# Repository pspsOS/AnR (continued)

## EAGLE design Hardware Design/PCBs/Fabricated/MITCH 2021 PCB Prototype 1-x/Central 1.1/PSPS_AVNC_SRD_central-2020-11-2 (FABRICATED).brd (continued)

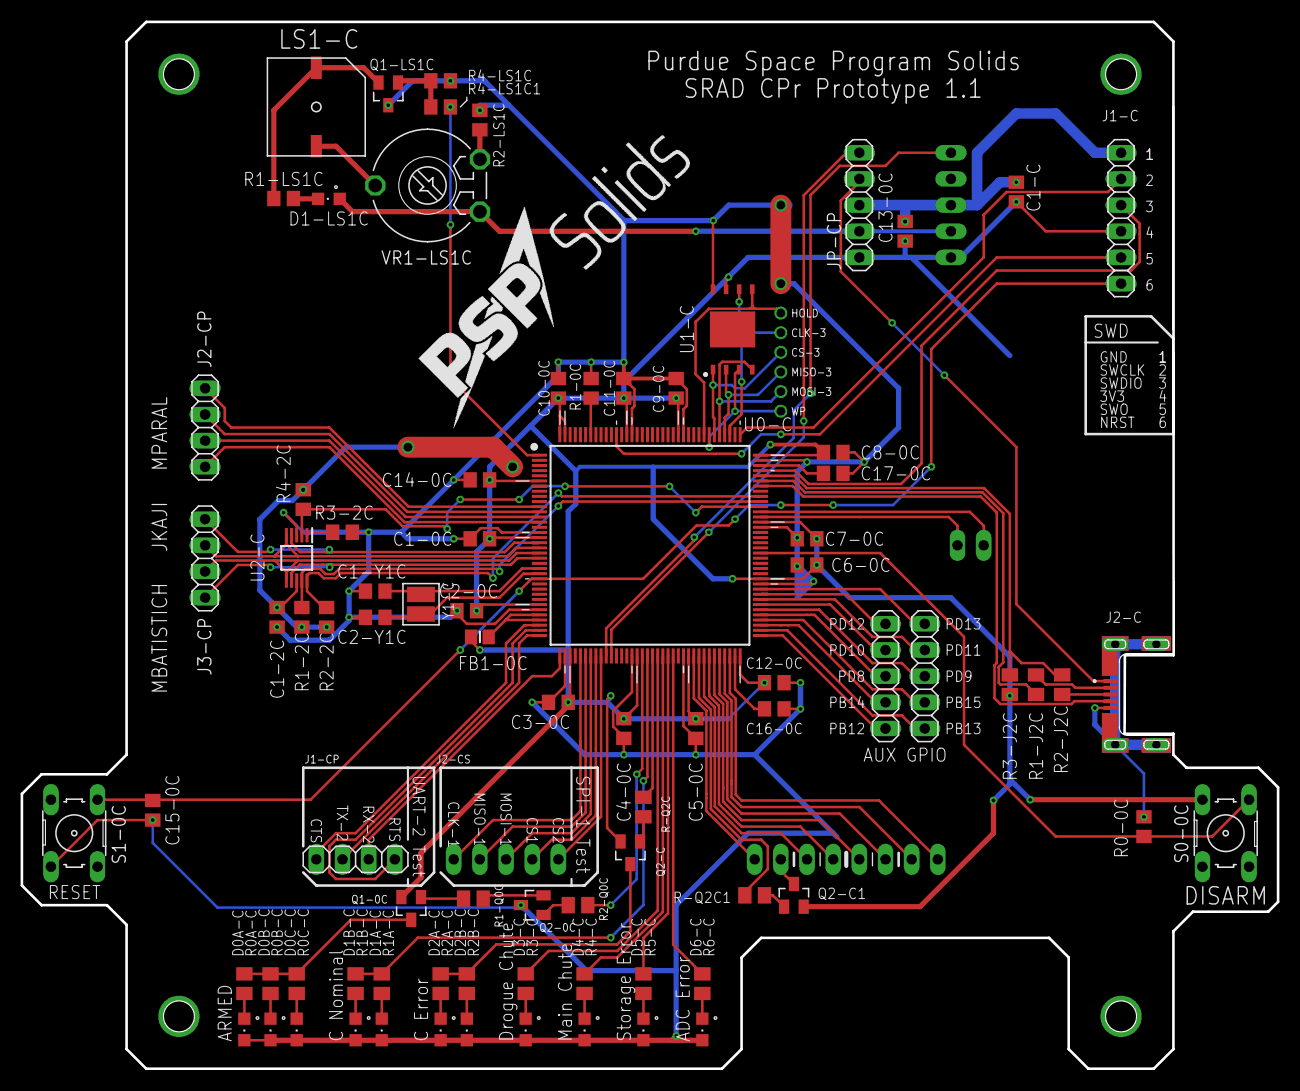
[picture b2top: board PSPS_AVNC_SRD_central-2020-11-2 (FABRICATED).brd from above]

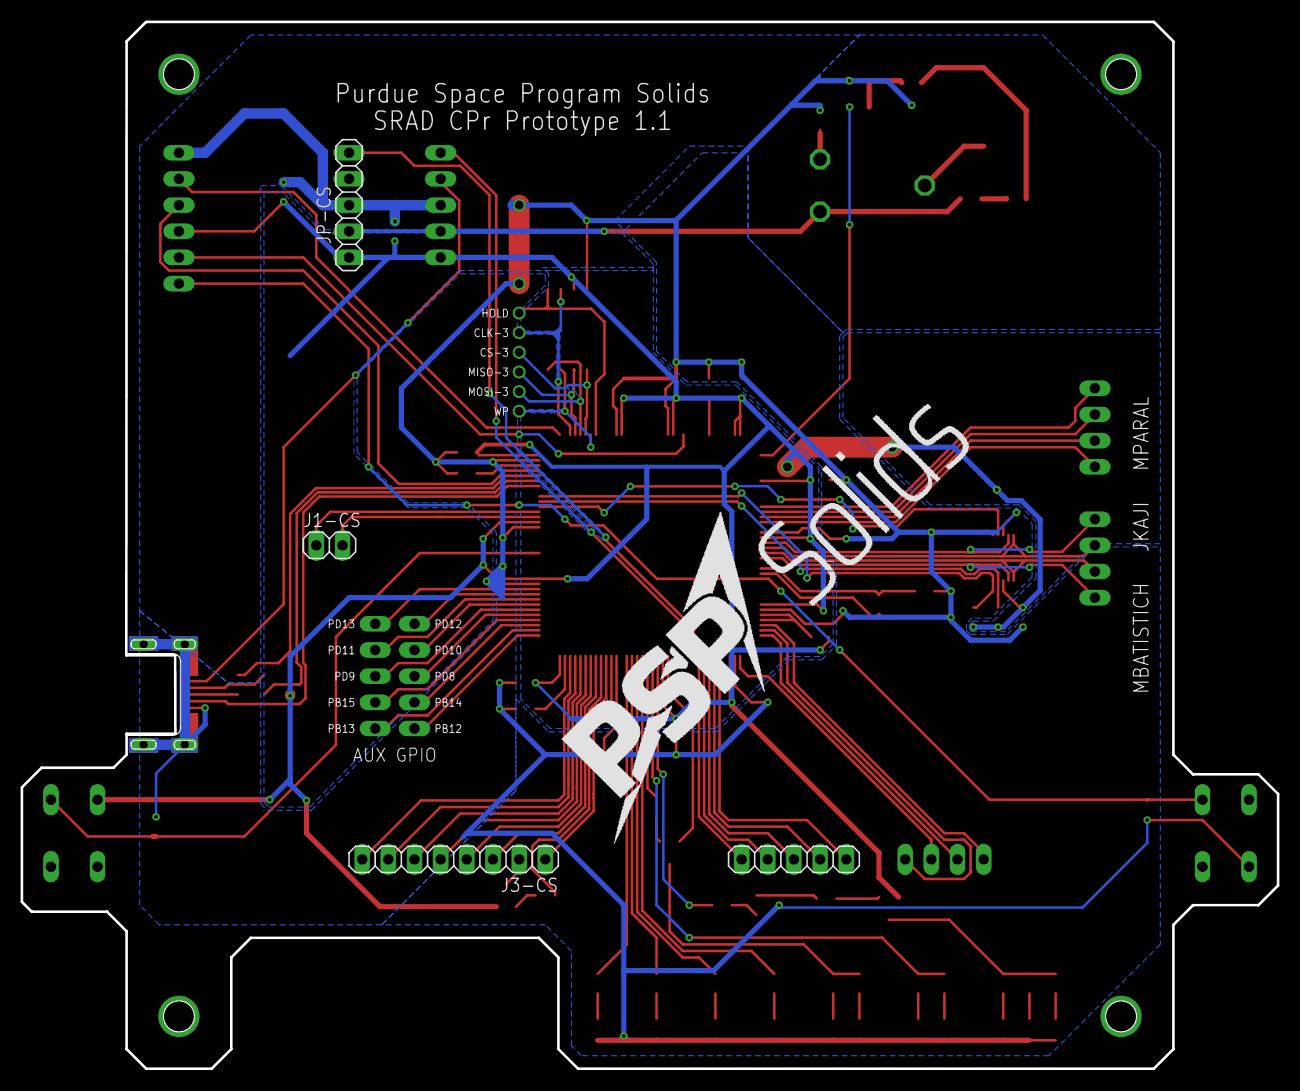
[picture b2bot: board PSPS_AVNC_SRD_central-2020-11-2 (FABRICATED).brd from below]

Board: 2 copper layers, 121.9 x 101.6 mm, 87 parts (4 on the bottom side), 101 nets.

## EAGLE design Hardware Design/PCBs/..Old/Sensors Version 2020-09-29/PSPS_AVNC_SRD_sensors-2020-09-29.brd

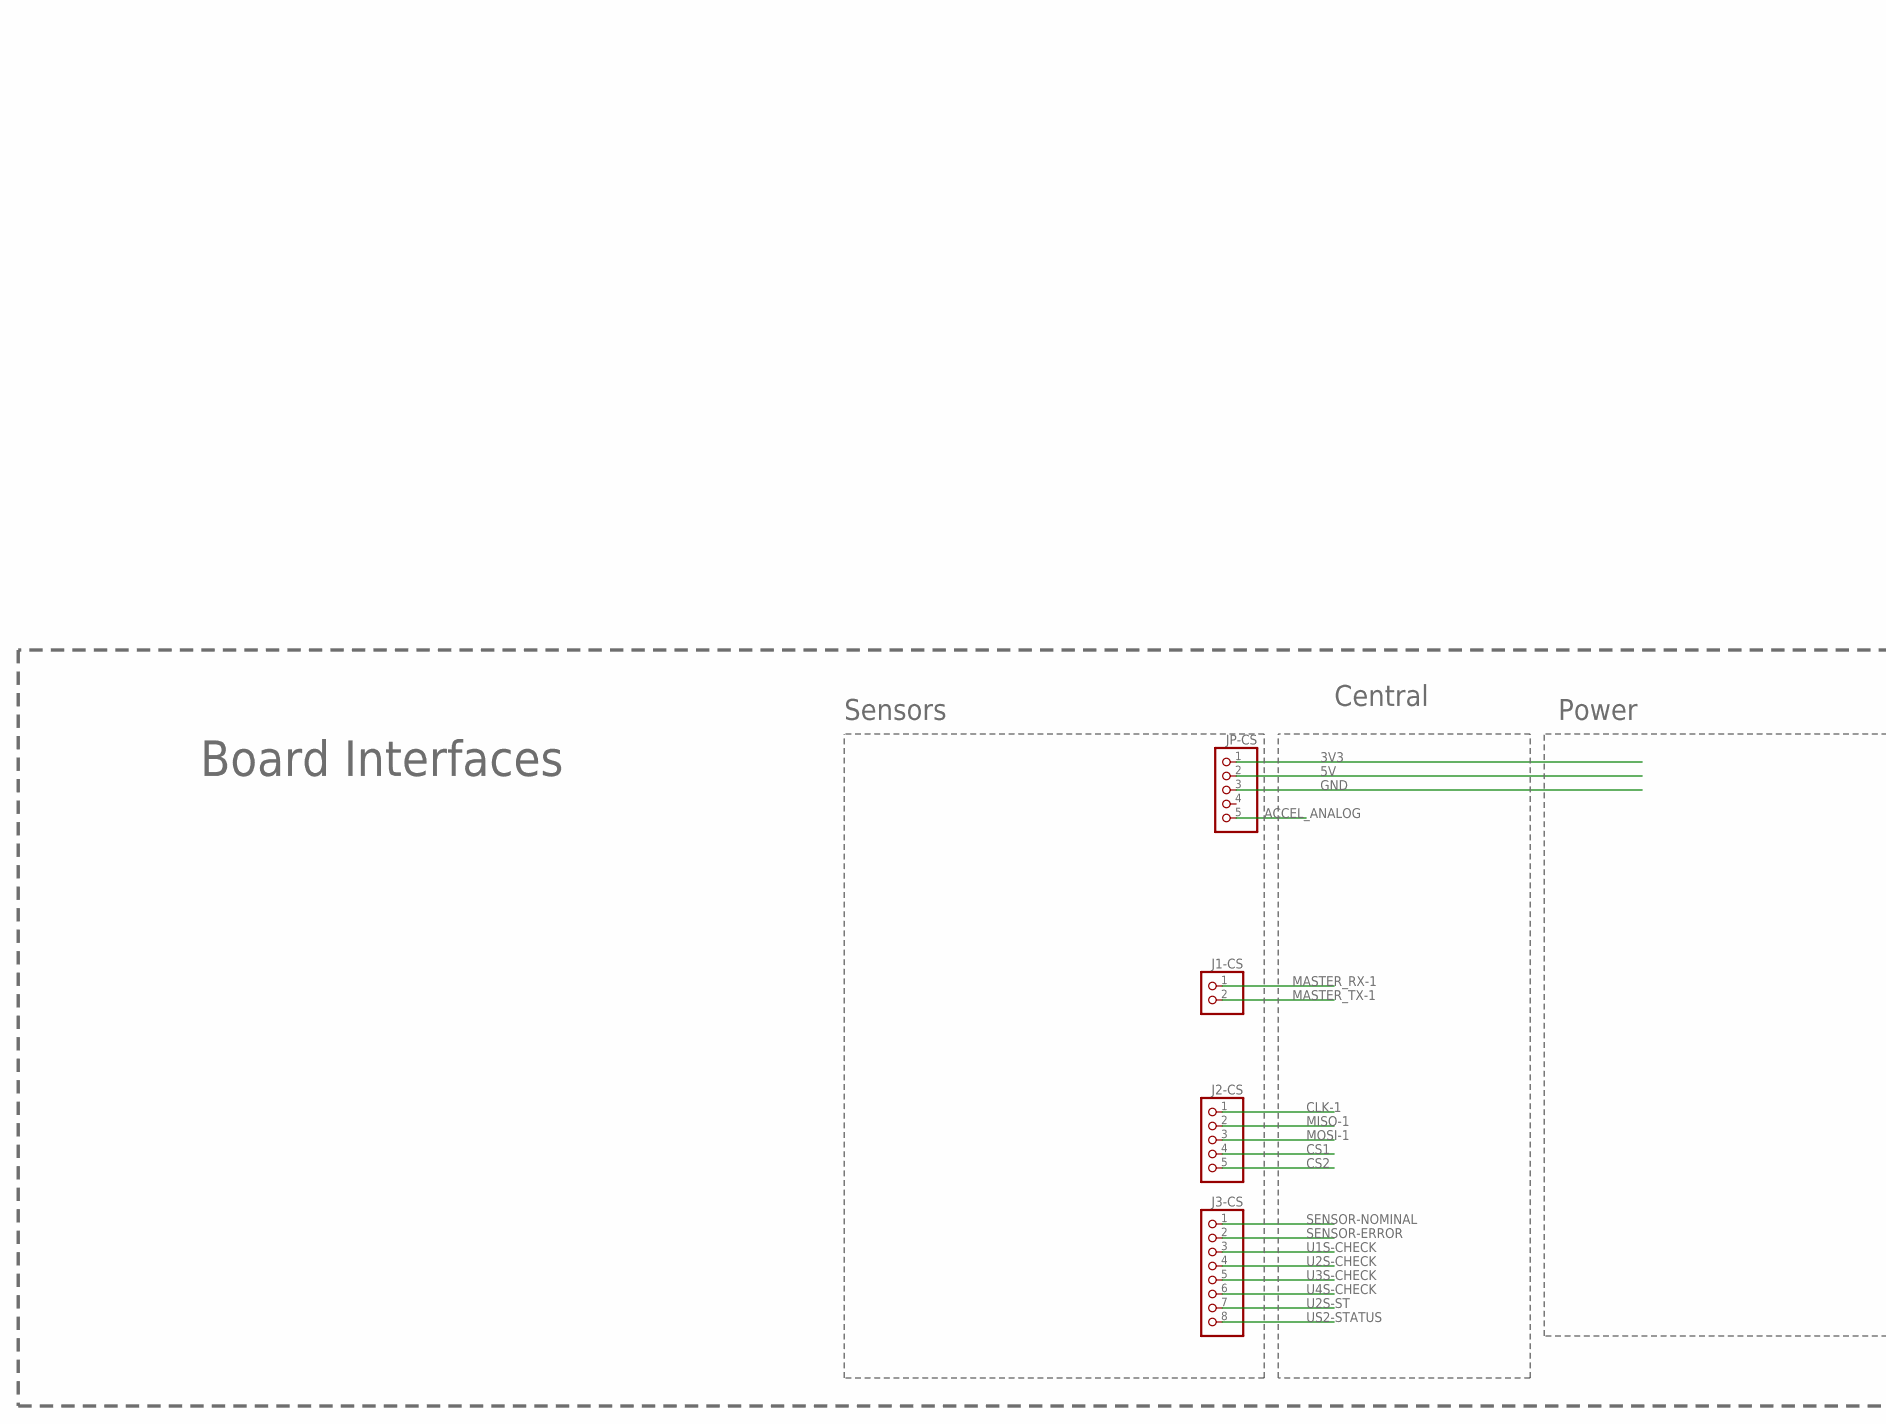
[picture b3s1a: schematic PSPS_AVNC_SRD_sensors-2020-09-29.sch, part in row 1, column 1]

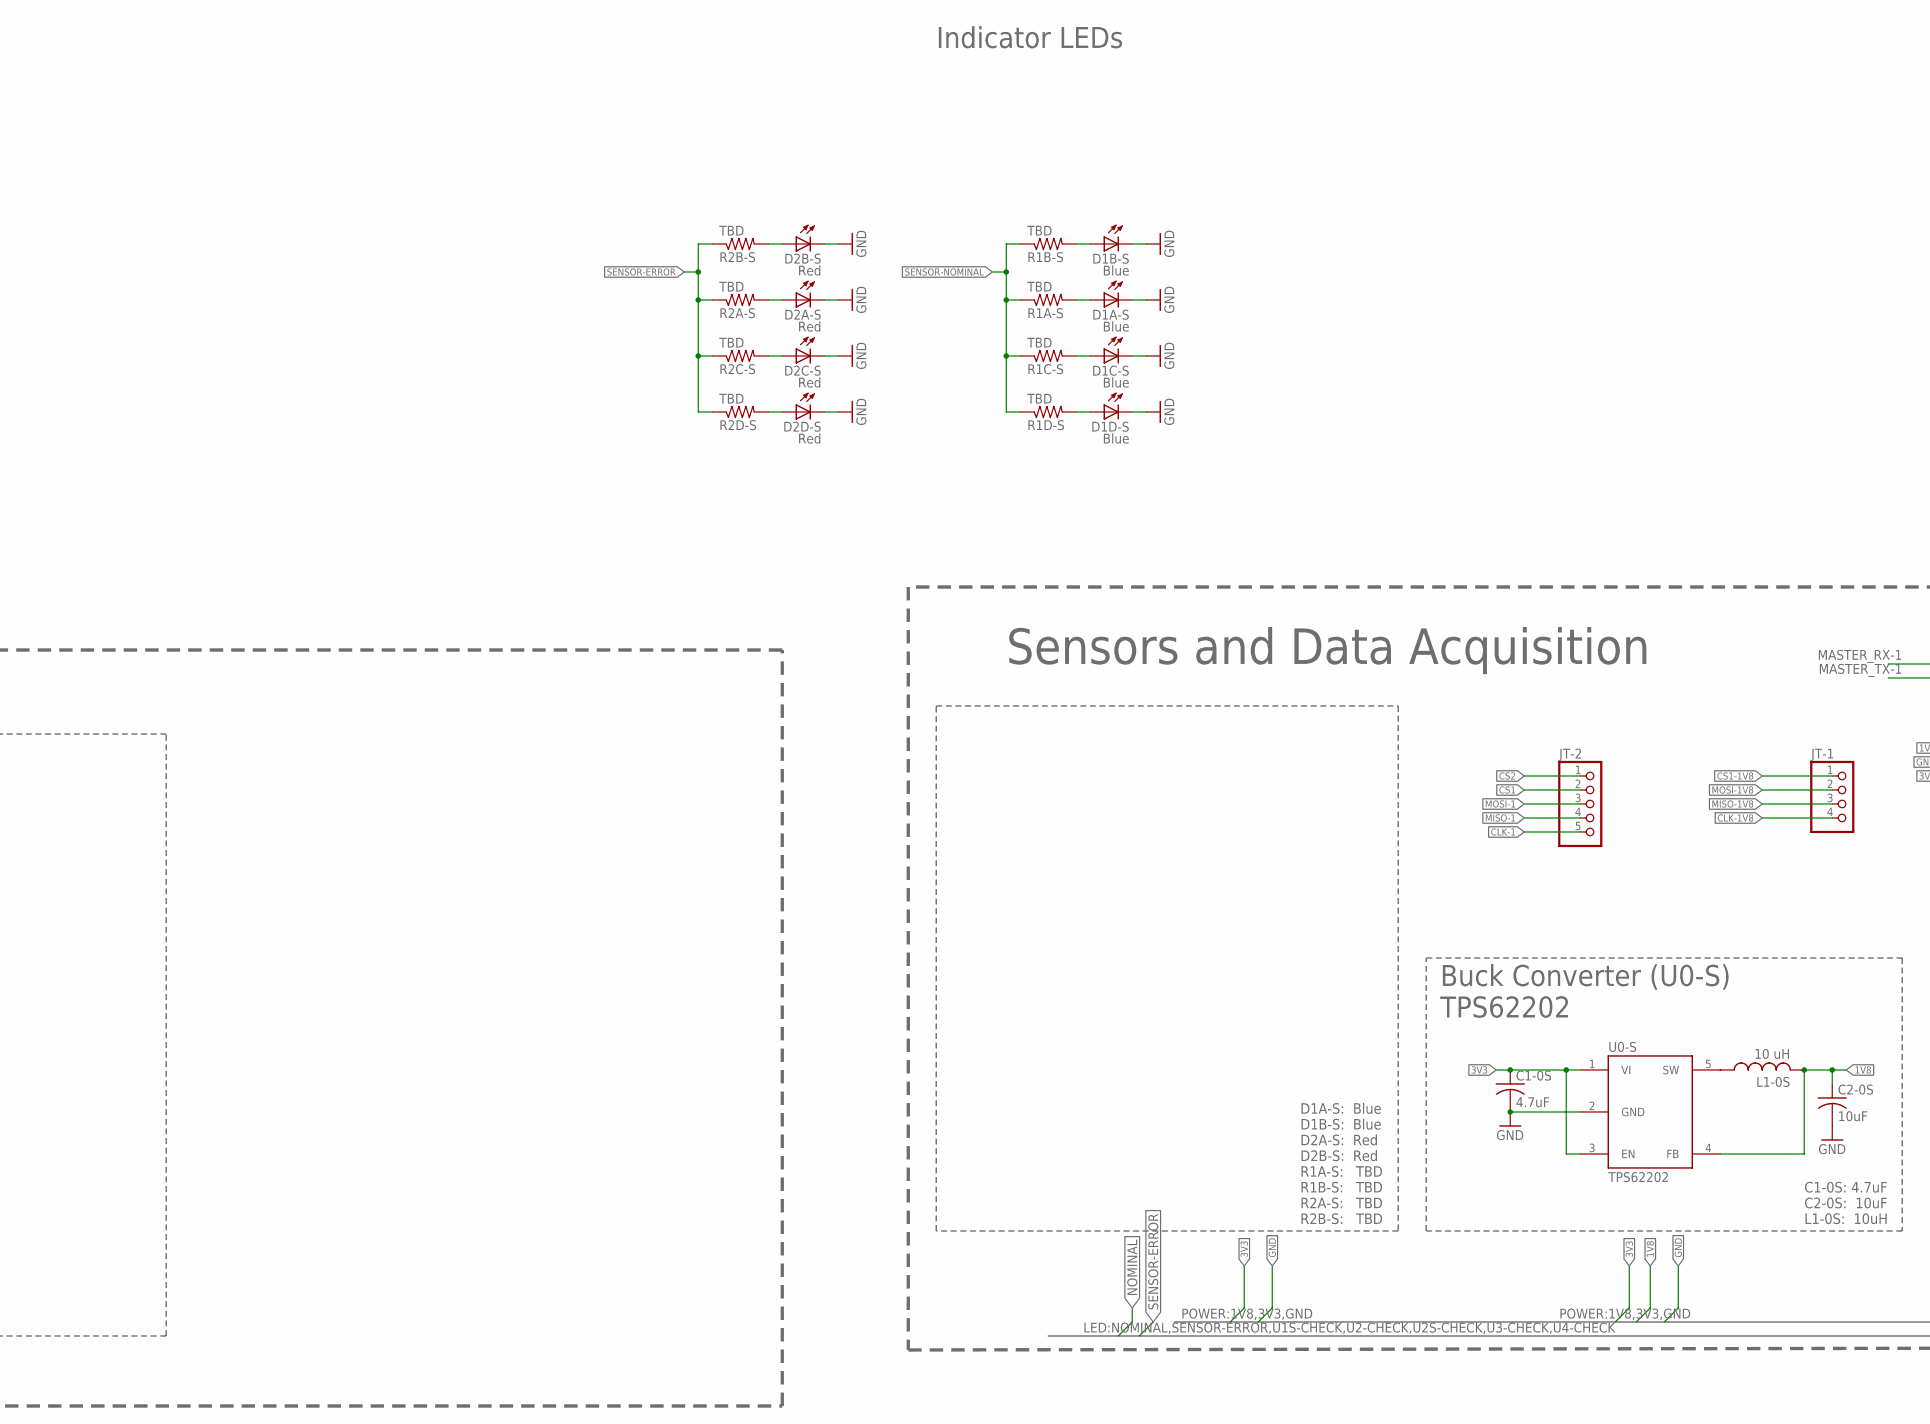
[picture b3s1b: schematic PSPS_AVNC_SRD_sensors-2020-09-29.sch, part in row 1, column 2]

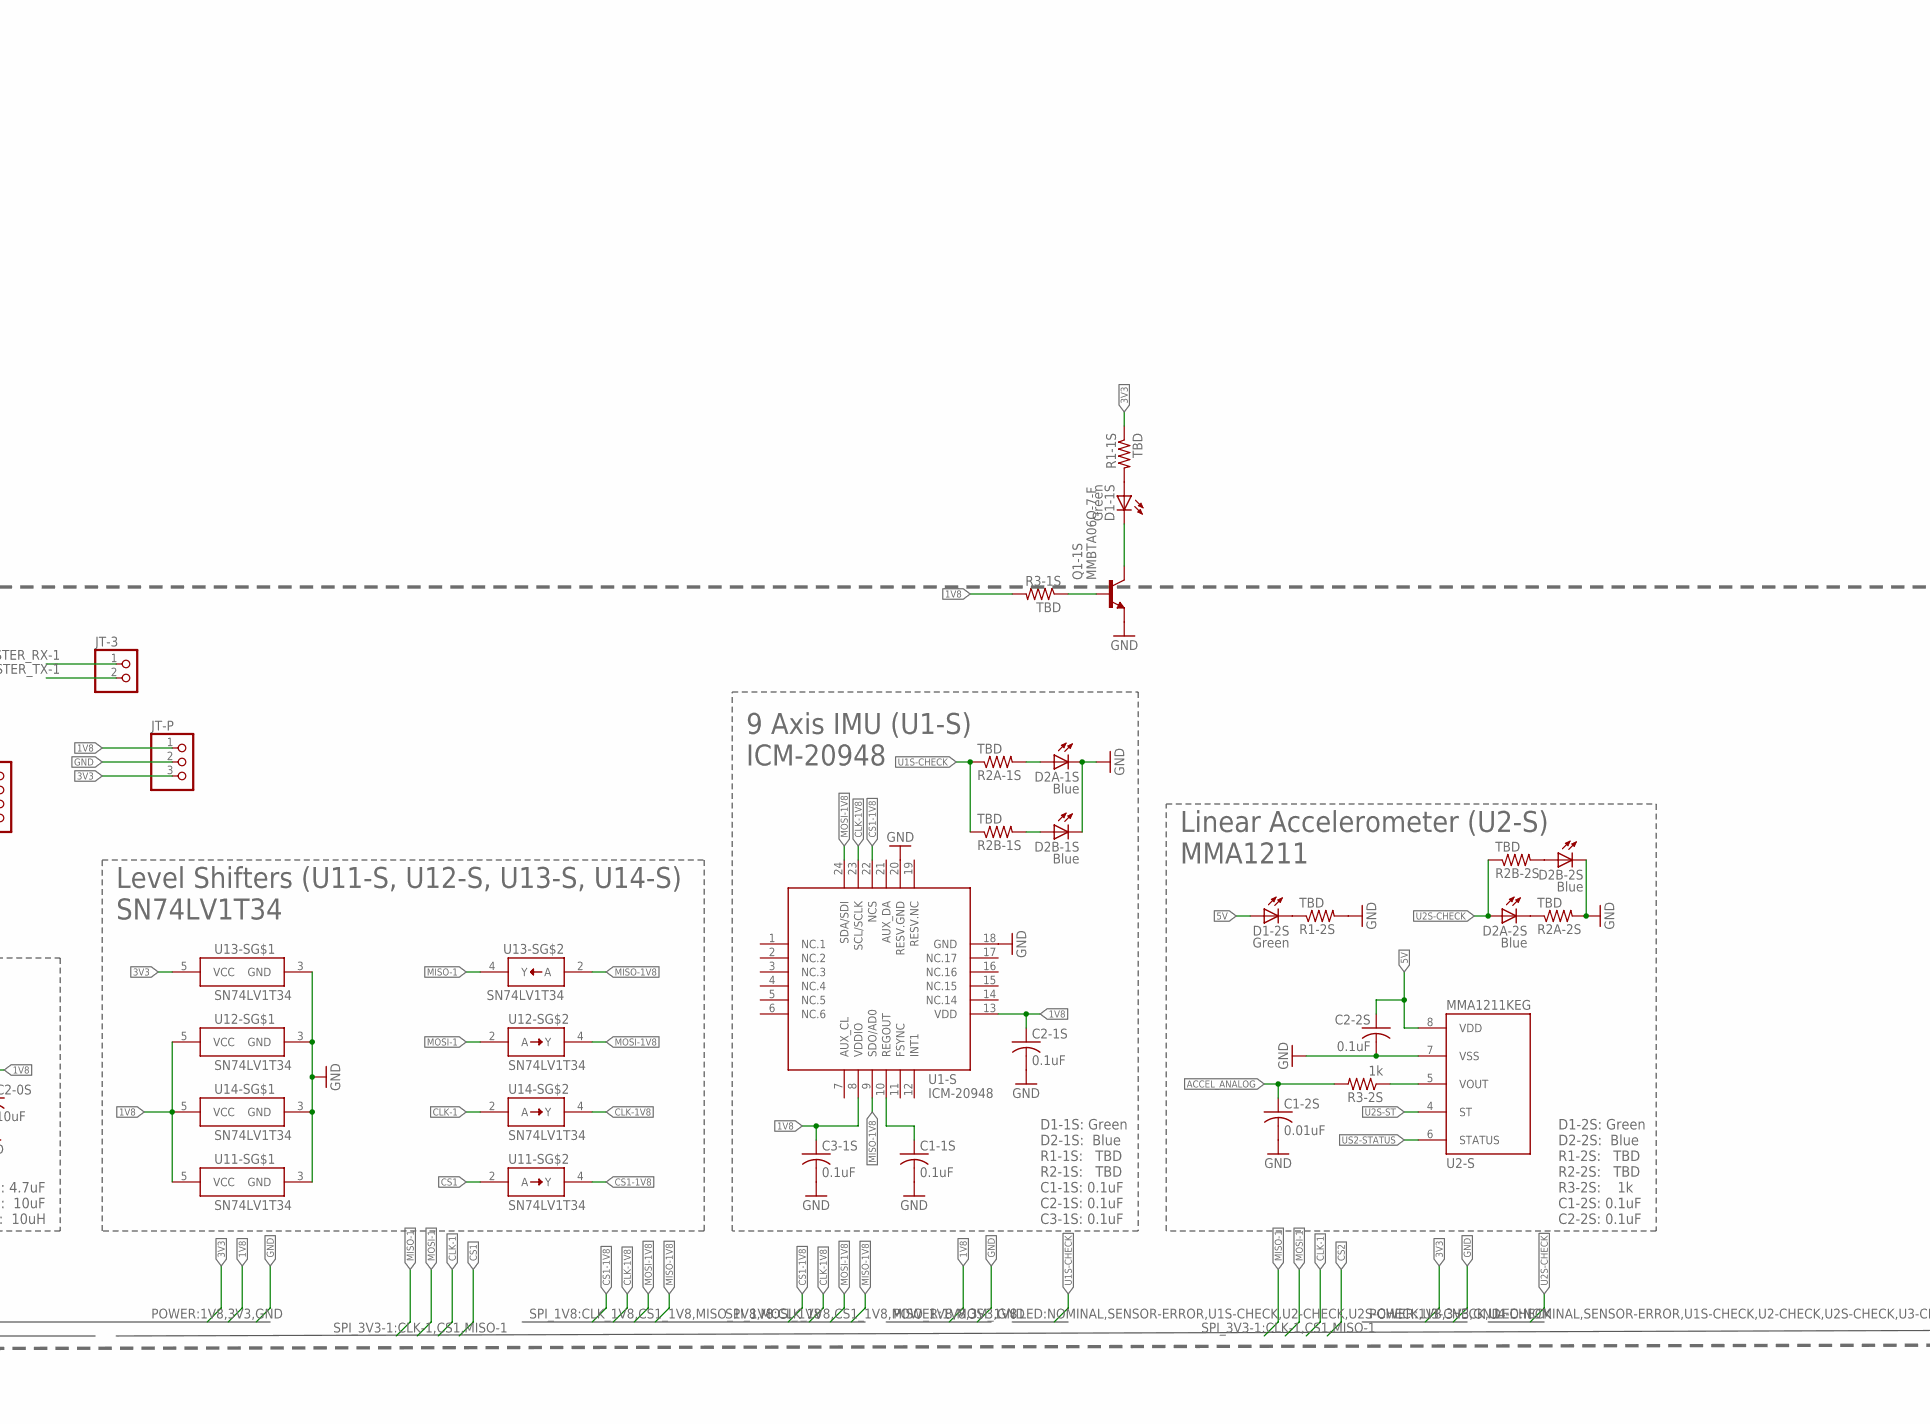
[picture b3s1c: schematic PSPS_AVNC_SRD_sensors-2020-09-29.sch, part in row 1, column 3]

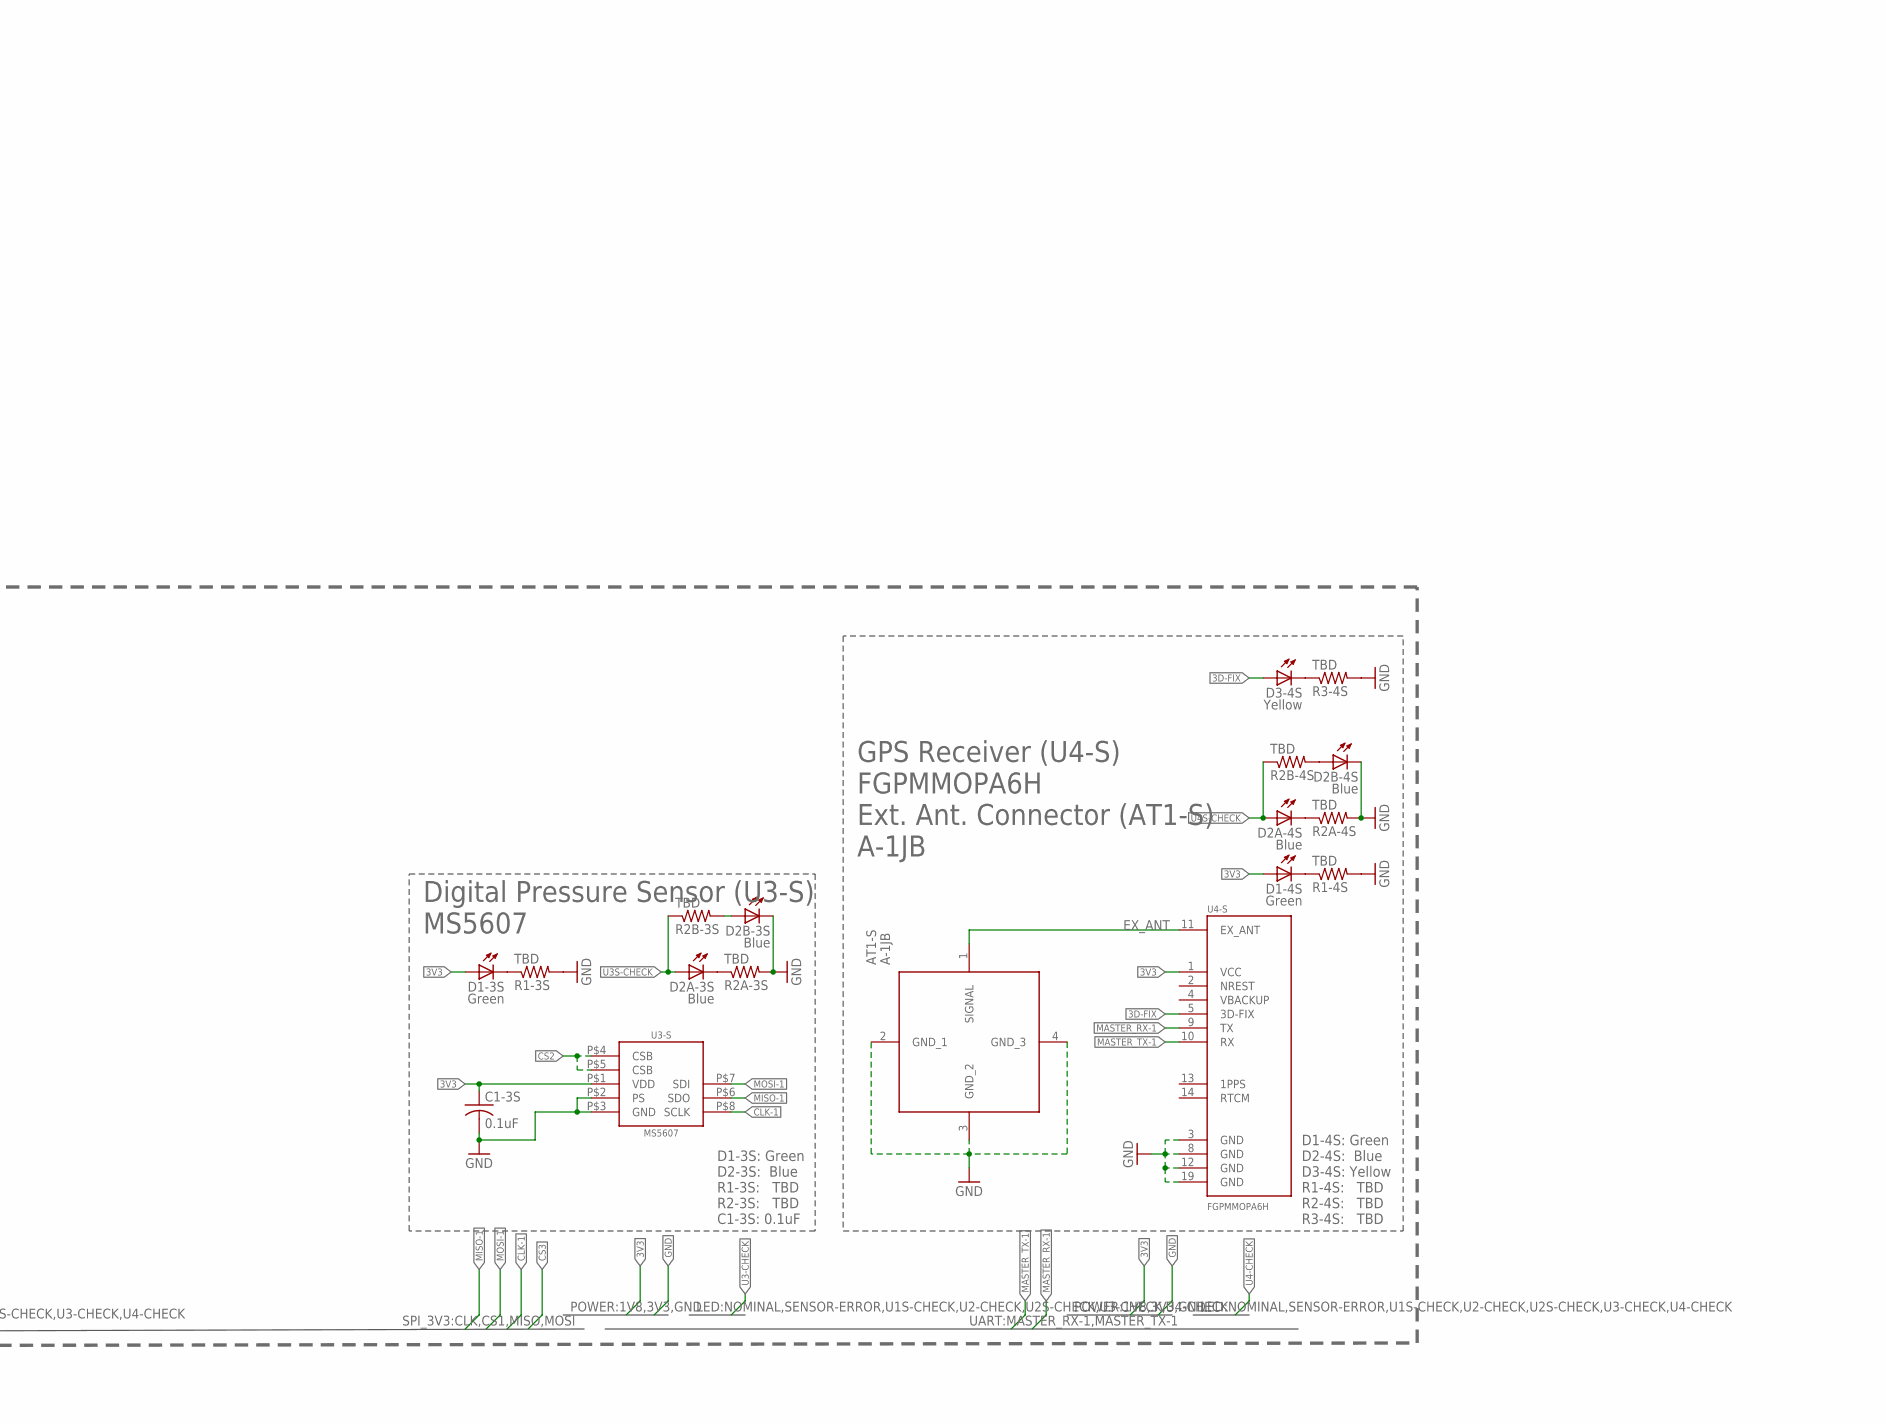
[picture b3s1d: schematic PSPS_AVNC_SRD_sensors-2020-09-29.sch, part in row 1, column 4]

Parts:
AT1-S: A-1JB; A1JB
C1-0S: 4.7uF; C0805
C1-1S, C1-3S, C2-1S, C2-2S, C3-1S: 0.1uF; C0805
C1-2S: 0.01uF; C0805
C2-0S: 10uF; C0805
D1-1S, D1-2S, D1-3S, D1-4S: Green; CHIPLED_0805
D1A-S, D1B-S, D1C-S, D1D-S, D2A-1S, D2A-2S, D2A-3S, D2A-4S, D2B-1S, D2B-2S, D2B-3S, D2B-4S: Blue; CHIPLED_0805
D2A-S, D2B-S, D2C-S, D2D-S: Red; CHIPLED_0805
D3-4S: Yellow; CHIPLED_0805
J1-CS: PINHD-1X2; 1X02
J2-CS: PINHD-1X5; 1X05
J3-CS: PINHD-1X8; 1X08
JP-CS: PINHD-1X5; 1X05
JT-1: PINHD-1X4; 1X04
JT-2: PINHD-1X5; 1X05
JT-3: PINHD-1X2; 1X02
JT-P: PINHD-1X3; 1X03
L1-0S: 10 uH; L1812
Q1-1S: MMBTA06Q-7-F; SOT23
R1-1S, R1-2S, R1-3S, R1-4S, R1A-S, R1B-S, R1C-S, R1D-S, R2A-1S, R2A-2S, R2A-3S, R2A-4S, R2A-S, R2B-1S, R2B-2S, R2B-3S, R2B-4S, R2B-S, R2C-S, R2D-S, R3-1S, R3-4S: TBD; R0805
R3-2S: 1k; R0805
U0-S: TPS62202; SOT95P280X145-5
U1-S: ICM-20948; QFN40P300X300X105-25T159X175
U2-S: MMA1211KEG; SOIC127P1041X355-16N
U3-S: MS5607
U4-S: FGPMMOPA6H; SOIC127P1800X470-20N
U11-S, U12-S, U13-S, U14-S: SN74LV1T34; SOT65P210X110-5

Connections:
1V8: C2-0S.1, C2-1S.1, C3-1S.1, JT-P.1, L1-0S.2, R3-1S.2, U0-S.4 (FB), U1-S.8 (VDDIO), U1-S.13 (VDD), U11-S.5 (VCC), U12-S.5 (VCC), U14-S.5 (VCC)
3D-FIX: D3-4S.A, U4-S.5 (3D-FIX)
3V3: C1-0S.1, C1-3S.1, D1-3S.A, D1-4S.A, JP-CS.1, JT-P.3, R1-1S.1, U0-S.1 (VI), U0-S.3 (EN), U3-S.P$1 (VDD), U4-S.1 (VCC), U13-S.5 (VCC)
5V: C2-2S.1, D1-2S.A, JP-CS.2, U2-S.8 (VDD)
ACCEL_ANALOG: C1-2S.1, JP-CS.5, R3-2S.2
CLK-1: J2-CS.1, JT-2.5, U3-S.P$8 (SCLK), U14-S.2 (A)
CLK-1V8: JT-1.4, U1-S.23 (SCL/SCLK), U14-S.4 (Y)
CS1: J2-CS.4, JT-2.2, U11-S.2 (A)
CS1-1V8: JT-1.1, U1-S.22 (NCS), U11-S.4 (Y)
CS2: J2-CS.5, JT-2.1, U3-S.P$4 (CSB), U3-S.P$5 (CSB)
D1-2S_R1-2S: D1-2S.C, R1-2S.1
D1-3S_R1-3S: D1-3S.C, R1-3S.1
D1-4S_R1-4S: D1-4S.C, R1-4S.1
D2A-2S_R2A-2S: D2A-2S.C, R2A-2S.1
D2A-3S_R2A-3S: D2A-3S.C, R2A-3S.1
D2A-4S_R2A-4S: D2A-4S.C, R2A-4S.1
D3-4S_R3-4S: D3-4S.C, R3-4S.1
EX_ANT: AT1-S.1 (SIGNAL), U4-S.11 (EX_ANT)
GND: AT1-S.2 (GND_1), AT1-S.3 (GND_2), AT1-S.4 (GND_3), C1-0S.2, C1-1S.2, C1-2S.2, C1-3S.2, C2-0S.2, C2-1S.2, C2-2S.2, C3-1S.2, D1A-S.C, D1B-S.C, D1C-S.C, D1D-S.C, D2A-1S.C, D2A-S.C, D2B-1S.C, D2B-2S.C, D2B-3S.C, D2B-4S.C, D2B-S.C, D2C-S.C, D2D-S.C, JP-CS.3, JT-P.2, Q1-1S.3 (E), R1-2S.2, R1-3S.2, R1-4S.2, R2A-2S.2, R2A-3S.2, R2A-4S.2, R3-4S.2, U0-S.2 (GND), U1-S.18 (GND), U1-S.20 (RESV.GND), U2-S.7 (VSS), U3-S.P$2 (PS), U3-S.P$3 (GND), U4-S.3 (GND), U4-S.8 (GND), U4-S.12 (GND), U4-S.19 (GND), U11-S.3 (GND), U12-S.3 (GND), U13-S.3 (GND), U14-S.3 (GND)
MASTER_RX-1: J1-CS.1, JT-3.1, U4-S.9 (TX)
MASTER_TX-1: J1-CS.2, JT-3.2, U4-S.10 (RX)
MISO-1: J2-CS.2, JT-2.4, U3-S.P$6 (SDO), U13-S.4 (Y)
MISO-1V8: JT-1.3, U1-S.9 (SDO/AD0), U13-S.2 (A)
MOSI-1: J2-CS.3, JT-2.3, U3-S.P$7 (SDI), U12-S.2 (A)
MOSI-1V8: JT-1.2, U1-S.24 (SDA/SDI), U12-S.4 (Y)
R1-1S_Q1-1S: D1-1S.C, Q1-1S.2 (C)
R1A-S_D1A-S: D1A-S.A, R1A-S.2
R1B-S_D1B-S: D1B-S.A, R1B-S.2
R1C-S_D1C-S: D1C-S.A, R1C-S.2
R1D-S_D1D-S: D1D-S.A, R1D-S.2
R2-1S_D1-1S: D1-1S.A, R1-1S.2
R2A-1S_D2A-1S: D2A-1S.A, R2A-1S.2
R2A-S_D2A-S: D2A-S.A, R2A-S.2
R2B-1S_D2B-1S: D2B-1S.A, R2B-1S.2
R2B-2S_D2B-2S: D2B-2S.A, R2B-2S.2
R2B-3S_D2B-3S: D2B-3S.A, R2B-3S.2
R2B-4S_D2B-4S: D2B-4S.A, R2B-4S.2
R2B-S_D2B-S: D2B-S.A, R2B-S.2
R2C-S_D2C-S: D2C-S.A, R2C-S.2
R2D-S_D2D-S: D2D-S.A, R2D-S.2
R3-1S_Q1-1S: Q1-1S.1 (B), R3-1S.1
REGOUT: C1-1S.1, U1-S.10 (REGOUT)
SENSOR-ERROR: J3-CS.2, R2A-S.1, R2B-S.1, R2C-S.1, R2D-S.1
SENSOR-NOMINAL: J3-CS.1, R1A-S.1, R1B-S.1, R1C-S.1, R1D-S.1
U0S-SW: L1-0S.1, U0-S.5 (SW)
U1S-CHECK: J3-CS.3, R2A-1S.1, R2B-1S.1
U2S-CHECK: D2A-2S.A, J3-CS.4, R2B-2S.1
U2S-ST: J3-CS.7, U2-S.4 (ST)
U3S-CHECK: D2A-3S.A, J3-CS.5, R2B-3S.1
U4S-CHECK: D2A-4S.A, J3-CS.6, R2B-4S.1
US2-STATUS: J3-CS.8, U2-S.6 (STATUS)
VOUT: R3-2S.1, U2-S.5 (VOUT)

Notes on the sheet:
Level Shifters (U11-S, U12-S, U13-S, U14-S) SN74LV1T34
9 Axis IMU (U1-S) ICM-20948
Buck Converter (U0-S) TPS62202
C1-0S: 4.7uF C2-0S: 10uF L1-0S: 10uH
D1-1S: Green D2-1S: Blue R1-1S: TBD R2-1S: TBD C1-1S: 0.1uF C2-1S: 0.1uF C3-1S: 0.1uF
Linear Accelerometer (U2-S) MMA1211
D1-2S: Green D2-2S: Blue R1-2S: TBD R2-2S: TBD R3-2S: 1k C1-2S: 0.1uF C2-2S: 0.1uF
Digital Pressure Sensor (U3-S) MS5607
D1-3S: Green D2-3S: Blue R1-3S: TBD R2-3S: TBD C1-3S: 0.1uF
GPS Receiver (U4-S) FGPMMOPA6H Ext. Ant. Connector (AT1-S) A-1JB
D1-4S: Green D2-4S: Blue D3-4S: Yellow R1-4S: TBD R2-4S: TBD R3-4S: TBD
D1A-S: Blue D1B-S: Blue D2A-S: Red D2B-S: Red R1A-S: TBD R1B-S: TBD R2A-S: TBD R2B-S: TBD
Indicator LEDs
Sensors and Data Acquisition
Central
Power
Sensors
Board Interfaces

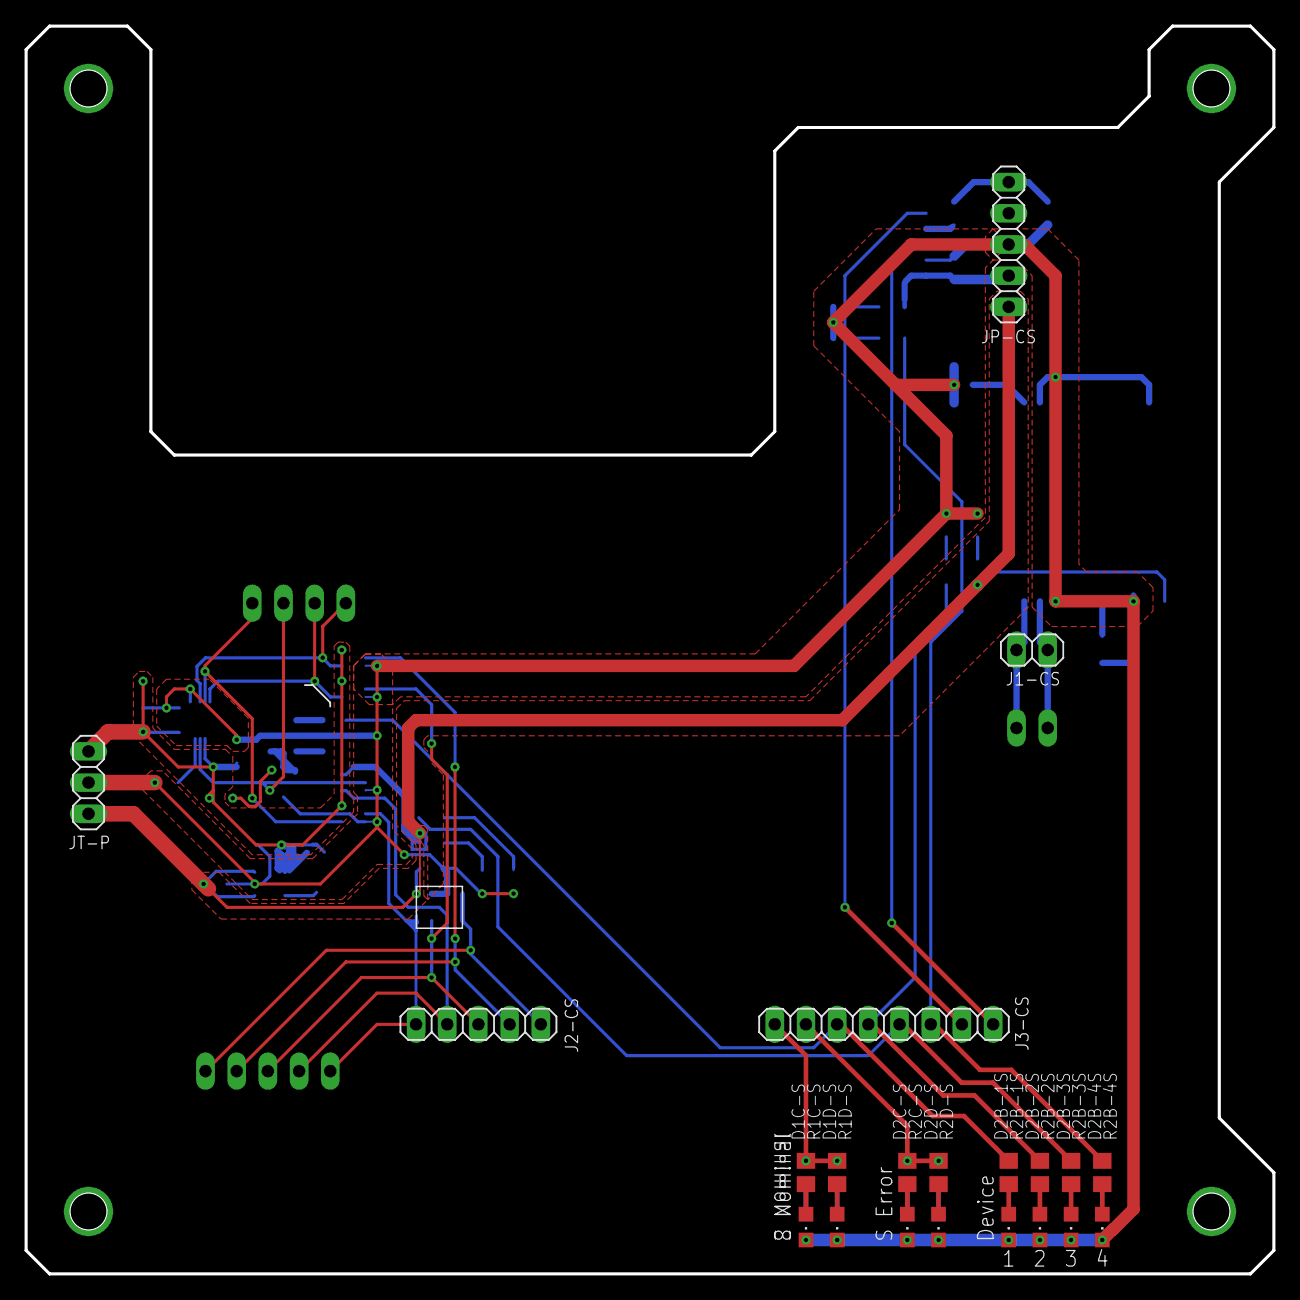
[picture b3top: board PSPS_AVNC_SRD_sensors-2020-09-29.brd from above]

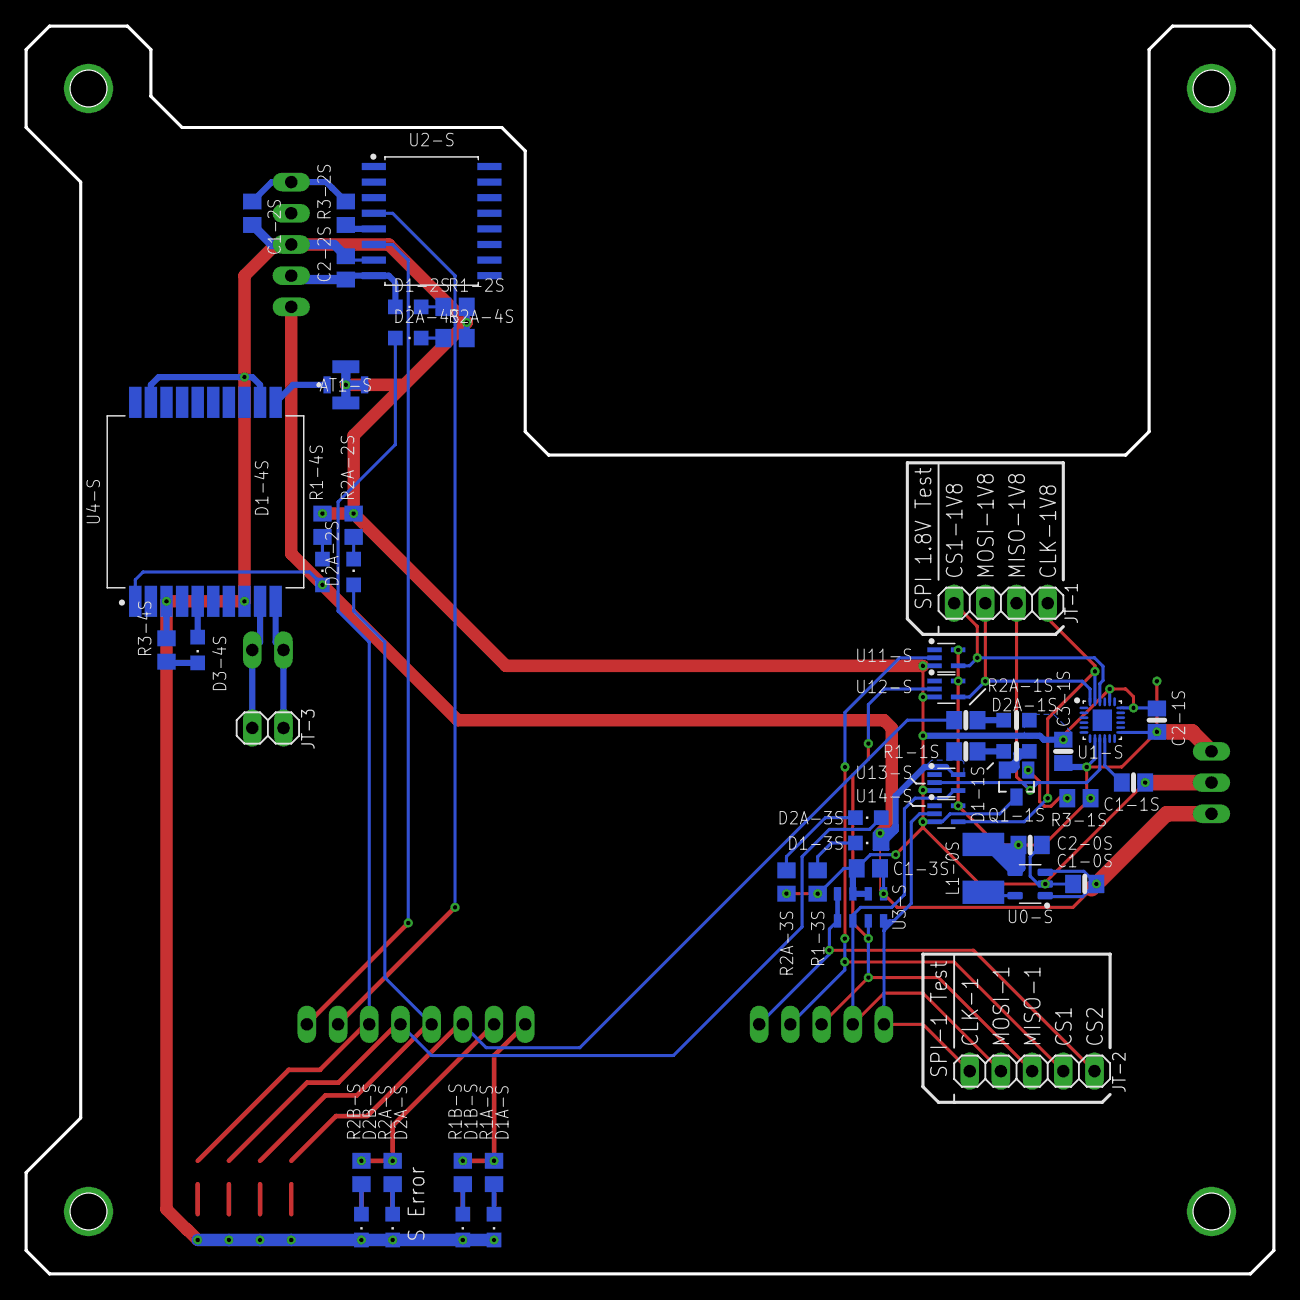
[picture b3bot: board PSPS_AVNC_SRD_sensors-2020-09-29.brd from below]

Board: 2 copper layers, 101.6 x 101.6 mm, 72 parts (51 on the bottom side), 52 nets.
